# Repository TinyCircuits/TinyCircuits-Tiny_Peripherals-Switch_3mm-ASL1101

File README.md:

# TinyCircuits Tiny Peripheral Switch 3mm
# ASL1101 Rev2

The design files are located under design_files/ for the TinyCircuits ASL1101 Rev 2 PCB.  This is a Tiny peripheral board that has an 3mm sealed switch, along with pads to solder to.

Format is in Cadsoft Eagle format - Eagle version 6.2 was used for the original design.

For more infomation on this, check out the product page at TinyCircuits.com: https://tinycircuits.com/collections/tinylily/products/tinylily-switch-3mm

# License:

Design by TinyCircuits.
All design files are released under the Creative Commons Attribution Share-Alike 3.0 License, see the following link for details: http://creativecommons.org/licenses/by-sa/3.0

All text above must be included in any redistribution or derived design

This project uses designs and concepts developed as part of the Arduino project and the LilyPad project.  The TinyCircuits design files themselves (schematics, PCB and libraries) are not directly derived from these works' design files and have been created new, however the concepts and basic architecture behind the TinyDuino and TinyLily products are derived and we thank the hard work of the organizations below for their contributions to open-source hardware:
  
Original Arduino Uno Design by Team Arduino

LilyPad Arduino Design by Leah Buechley and Sparkfun Electronics

Please support the open-source hardware community

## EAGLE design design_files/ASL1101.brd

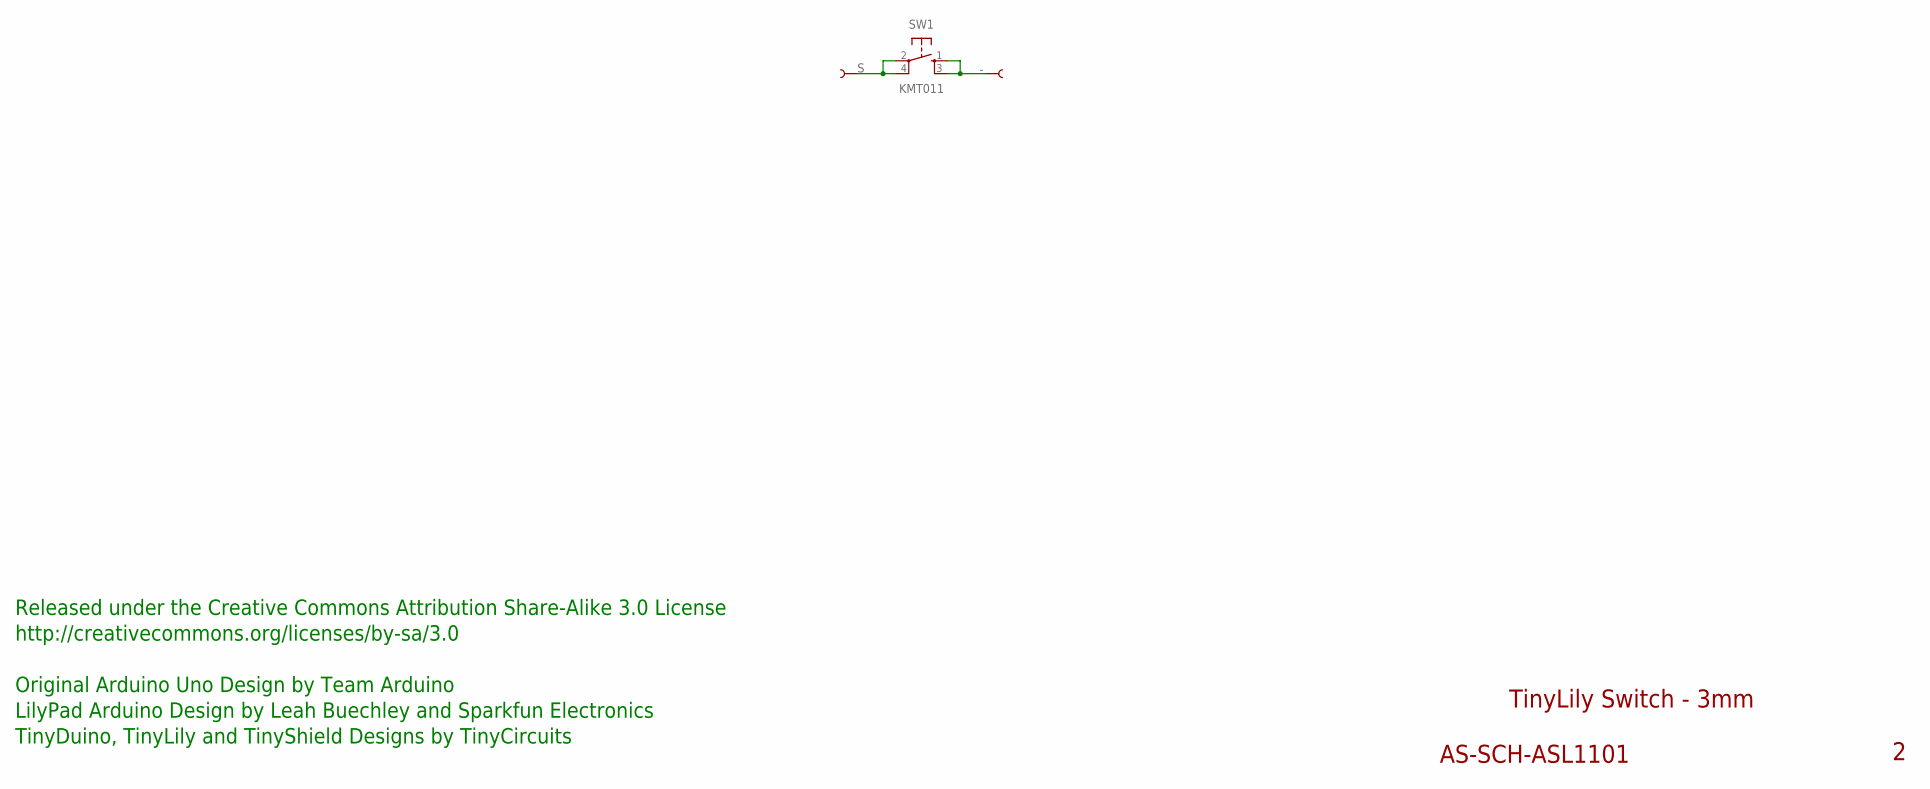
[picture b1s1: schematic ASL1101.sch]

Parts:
SW1: KMT011
U$1, U$7: SEWTABTH_1206; SEWTAP_TH_1206

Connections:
-: SW1.1, SW1.3, U$1.1
S: SW1.2, SW1.4, U$7.1

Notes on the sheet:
TinyLily Switch - 3mm
AS-SCH-ASL1101
Released under the Creative Commons Attribution Share-Alike 3.0 License
http://creativecommons.org/licenses/by-sa/3.0
Original Arduino Uno Design by Team Arduino
TinyDuino, TinyLily and TinyShield Designs by TinyCircuits
LilyPad Arduino Design by Leah Buechley and Sparkfun Electronics

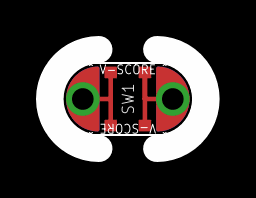
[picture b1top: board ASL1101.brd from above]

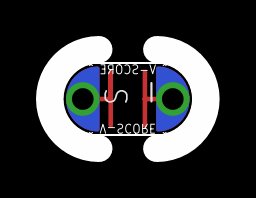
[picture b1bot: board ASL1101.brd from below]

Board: 2 copper layers, 8.7 x 5.5 mm, 4 parts (2 on the bottom side), 2 nets.

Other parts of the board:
U$6: DOCFIELD-TINYCIRCUITS-PCB

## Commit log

2013-06-30 Updated project link
2014-08-24 Updated Link
2019-01-04 update format
2020-08-28 Add CAD data
